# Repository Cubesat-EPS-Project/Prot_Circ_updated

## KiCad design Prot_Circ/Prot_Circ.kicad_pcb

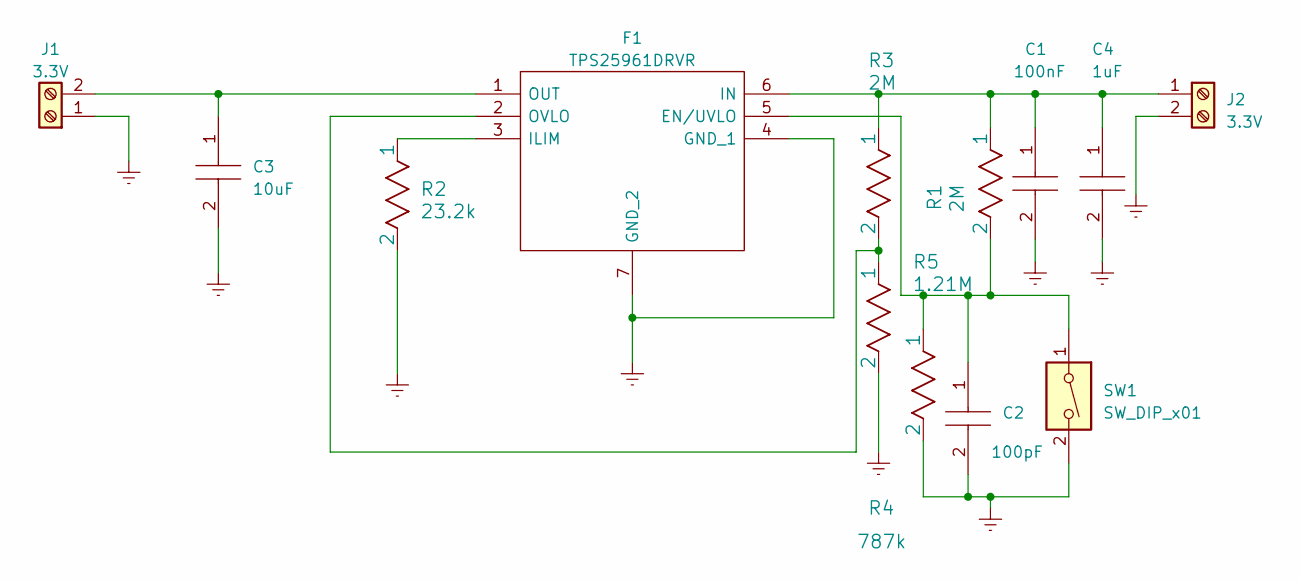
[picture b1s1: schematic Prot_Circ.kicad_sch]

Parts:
C1: 100nF; C1005_Commercial; Mouser Part Number 810-C1005X7R1C104K
C2: 100pF; CAPC1005X55N; Mouser Part Number 80-C0402C101K3RAUTO
C3: 10uF; CAPC2012X94N; Mouser Part Number 581-0805YC106KAT2A
C4: 1uF; C2220_FT; Mouser Part Number 80-C2220X105K2RAUTO
F1: TPS25961DRVR; SON65P200X200X80-7N; Mouser Part Number 595-TPS25961DRVR
J1, J2: 3.3V; TerminalBlock_Altech_AK300-2_P5.00mm
R1, R3: 2M; RC0603FR-072ML
R2: 23.2k; RC0603FR-072ML
R4: 787k; RC0603FR-072ML
R5: 1.21M; RC0603FR-072ML
SW1: SW_DIP_x01; SW_DIP_SPSTx01_Slide_6.7x4.1mm_W6.73mm_P2.54mm_LowProfile_J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

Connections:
Earth: C1.2, C2.2, C3.2, C4.2, F1.4 (GND_1), F1.7 (GND_2), J1.1, J2.2, R2.2, R4.2, R5.2, SW1.2
unnamed: C2.1, F1.5 (EN/UVLO), R1.2, R5.1, SW1.1
unnamed: F1.3 (ILIM), R2.1
unnamed: C1.1, C4.1, F1.6 (IN), J2.1, R1.1, R3.1
unnamed: C3.1, F1.1 (OUT), J1.2
unnamed: F1.2 (OVLO), R3.2, R4.1

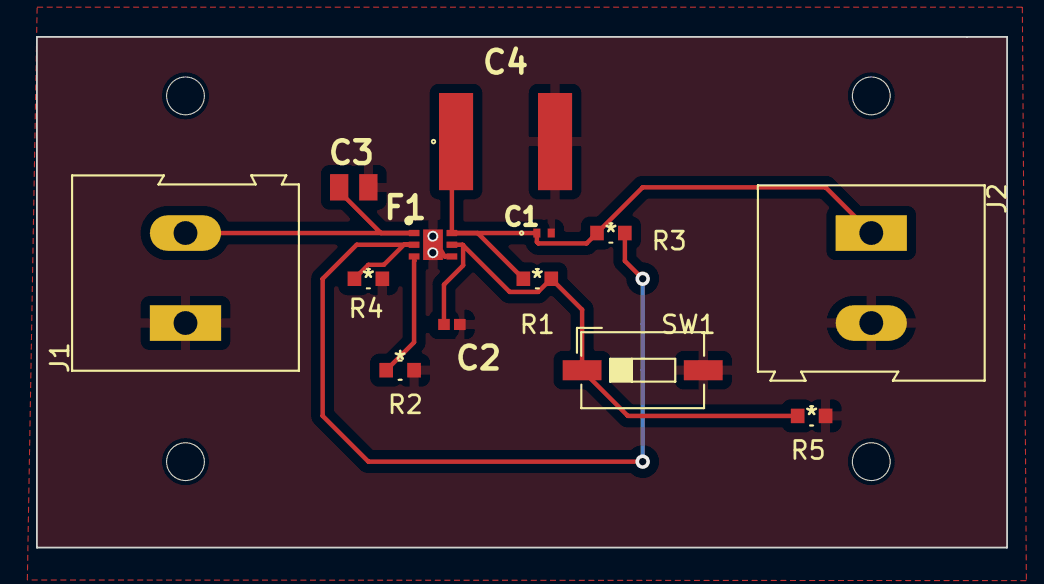
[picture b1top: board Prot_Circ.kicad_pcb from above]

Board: 2 copper layers, 53.9 x 28.4 mm, 13 parts (0 on the bottom side), 6 nets.

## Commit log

2023-02-20 Better protection board
    Schrmatic and PCB design of TPS25961 for protection
2023-02-20 Added Gerber Files
    Added gerber files and drill files

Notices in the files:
parts and their libraries:
Copyright 2021 Accelerated Designs. All rights reserved.
